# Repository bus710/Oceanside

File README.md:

# Oceanside

An integration project of RTOS, Golang application, and various clients.

## Maintainer
  
SJ Kim  
- Profile: [bus710.net](http://bus710.net)  
- Contact: <<bus710@gmail.com>>  

## Disclaimer

Using this project may cause various issue. Please consider your responsibility.

## Table of Contents
- Summary
- Hardware
- RTOS
- Golang Application 
- Clients
- Reference

## Summary

## Hardware

SBC, a bridge board, and a control board.

## RTOS

Chibios, threads, and the protocol.

## Golang Application

Termui, socket/websocket, and high performacne calcuration.

## Clients

Various clients such as ROS, LabVIEW, Unity3D, and so on.

## Reference

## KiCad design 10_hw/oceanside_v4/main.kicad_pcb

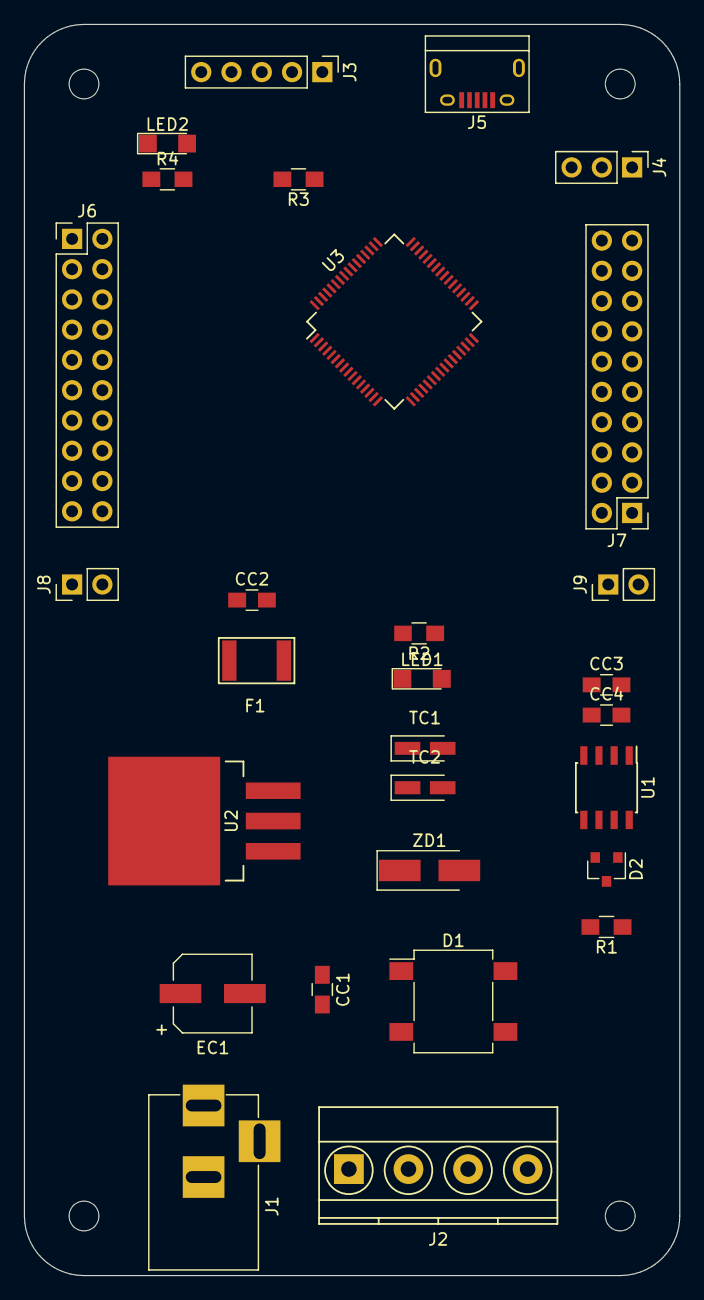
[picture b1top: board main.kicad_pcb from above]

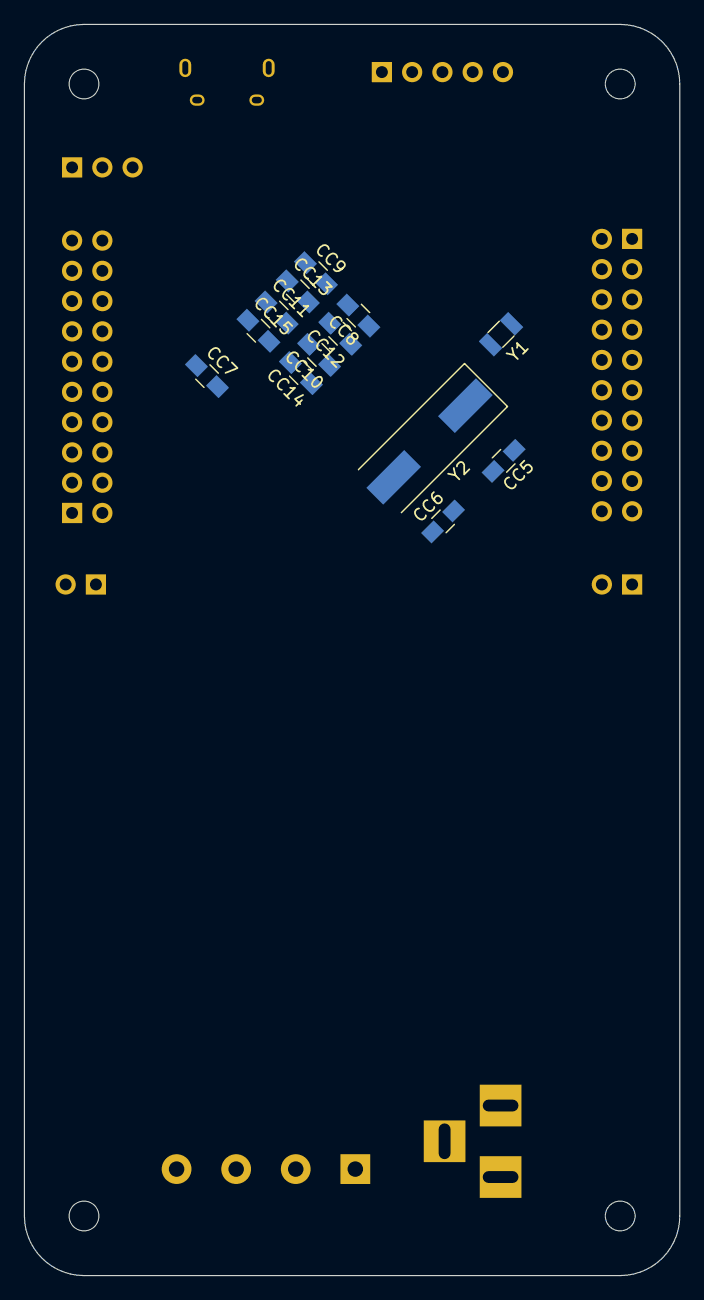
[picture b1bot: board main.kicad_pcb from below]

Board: 2 copper layers, 55.0 x 105.0 mm, 42 parts (13 on the bottom side), 60 nets, no tracks yet.

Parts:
CC1, CC2, CC3, CC8, CC9, CC10, CC11: 1uF; C_0805_HandSoldering
CC4, CC12, CC13, CC14, CC15: 4.7uF; C_0805_HandSoldering
CC5, CC6: 15pF; C_0805_HandSoldering
CC7: 2.2uF; C_0805_HandSoldering
D1: DF01S (OnSemi) +-AA; Diode_Bridge_DFS
D2: SM712; SOT-23
EC1: 47uF; CP_Elec_6.3x4.5
F1: FUSE(PTS18126V300); FusePTS1812
J1: BARREL_JACK
J2: VehicleCON; TerminalBlock_Pheonix_MKDS1.5-4pol
J3: SWDCON; Pin_Header_Straight_1x05_Pitch2.54mm
J4: SerialConsole; Pin_Header_Straight_1x03_Pitch2.54mm
J5: MiniUSB; USB_Micro-B
J6: GPIO_1; Pin_Header_Straight_2x10_Pitch2.54mm
J7: GPIO_2; Pin_Header_Straight_2x10_Pitch2.54mm
J8, J9: 3V3; Pin_Header_Straight_1x02_Pitch2.54mm
LED1, LED2: LED; LED_1206
R1: 120; R_0805_HandSoldering
R2, R4: 200; R_0805_HandSoldering
R3: 10k; R_0805_HandSoldering
TC1, TC2: 10uF; CP_Tantalum_Case-A_EIA-3216-18_Wave
U1: SN65HVD233-HT; SOIC-8_3.9x4.9mm_Pitch1.27mm
U2: LM1085-3.3/TO263; TO-263-3Lead_re
U3: STM32F446R; LQFP-64_10x10mm_Pitch0.5mm
Y1: 32k; Crystal_SMD_3215-2pin_3.2x1.5mm
Y2: 8M; Crystal_SMD_HC49-SD
ZD1: BZG05C12; D_SMA_Handsoldering

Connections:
+3V3: CC2.1, CC3.1, CC4.1, CC8.1, CC9.1, CC10.1, CC11.1, CC12.1, CC13.1, CC14.1, CC15.1, F1.1, J3.1, J8.1, J9.1, R2.2, R3.1, U1.3, U3.1, U3.13, U3.19, U3.32, U3.48, U3.64
/Battery+: D1.3, J1.1, J2.1
/SUB_F446/NRST: J3.5, R3.2, U3.7
/SUB_F446/OSC32_1: U3.3, Y1.2
/SUB_F446/OSC32_2: U3.4, Y1.1
/SUB_F446/OSC_1: CC5.1, U3.5, Y2.1
/SUB_F446/OSC_2: CC6.1, U3.6, Y2.2
/SUB_F446/P0: J6.1, U3.50
/SUB_F446/P1: J6.2, U3.51
/SUB_F446/P2: J6.3, U3.52
/SUB_F446/P3: J6.4, U3.53
/SUB_F446/P4: J6.5, U3.54
/SUB_F446/P5: J6.6, U3.55
/SUB_F446/P6: J6.7, U3.56
/SUB_F446/P7: J6.8, U3.57
/SUB_F446/P8: J6.9, U3.58
/SUB_F446/P9: J6.10, U3.59
/SUB_F446/P10: J6.11, U3.8
/SUB_F446/P11: J6.12, U3.9
/SUB_F446/P12: J6.13, U3.10
/SUB_F446/P13: J6.14, U3.11
/SUB_F446/P14: J6.15, U3.14
/SUB_F446/P15: J6.16, U3.15
/SUB_F446/P16: J6.17, U3.16
/SUB_F446/P17: J7.1, U3.17
/SUB_F446/P18: J7.2, U3.20
/SUB_F446/P19: J7.3, U3.21
/SUB_F446/P20: J7.4, U3.22
/SUB_F446/P21: J7.5, U3.23
/SUB_F446/P22: J7.6, U3.24
/SUB_F446/P23: J7.7, U3.25
/SUB_F446/P24: J7.8, U3.26
/SUB_F446/P25: J7.9, U3.27
/SUB_F446/P26: J7.10, U3.29
/SUB_F446/P27: J7.11, U3.33
/SUB_F446/P28: J7.12, U3.34
/SUB_F446/P29: J7.13, U3.35
/SUB_F446/P30: J7.14, U3.36
/SUB_F446/P31: J7.15, U3.37
/SUB_F446/P32: J7.16, U3.38
/SUB_F446/P33: J7.17, U3.39
/SUB_F446/P34: J7.18, U3.40
/SUB_F446/P35: J7.19, U3.41
/SUB_F446/STM_CAN1_RX: U1.4, U3.62
/SUB_F446/STM_CAN1_TX: U1.1, U3.61
/SUB_F446/SWCLK: J3.4, U3.49
/SUB_F446/SWDIO: J3.2, U3.46
/SUB_F446/SYS_LED: R4.1, U3.2
/SUB_F446/UART1_RX: J4.2, U3.43
/SUB_F446/UART1_TX: J4.1, U3.42
GND: CC1.2, CC2.2, CC3.2, CC4.2, CC5.2, CC6.2, CC7.2, CC8.2, CC9.2, CC10.2, CC11.2, CC12.2, CC13.2, CC14.2, CC15.2, D1.2, D1.4, D2.3, EC1.2, J1.2, J1.3, J2.2, J3.3, J4.3, J5.5, J5.6, J8.2, J9.2, LED1.1, LED2.1, TC1.2, TC2.2, U1.2, U1.8, U2.1, U3.12, U3.18, U3.28, U3.31, U3.47, U3.60, U3.63, ZD1.2
unnamed: CC1.1, D1.1, EC1.1, TC1.1, U2.3, ZD1.1
unnamed: CC7.1, U3.30
unnamed: D2.1, J2.3, R1.1, U1.7
unnamed: D2.2, J2.4, R1.2, U1.6
unnamed: F1.2, TC2.1, U2.2
unnamed: J5.2, U3.44
unnamed: J5.3, U3.45
unnamed: LED1.2, R2.1
unnamed: LED2.2, R4.2

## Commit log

2017-06-29 A minor update
2017-06-30 1st draft for readme.
2017-07-08 added the firmware.
2017-07-09 added uart feature but not tested yet.
2017-07-10 Rename 02_mbed.md to 02_chibios.md
2017-07-10 succeeded to activate CAN.
2017-07-10 added a comment about CAN1.
2017-07-10 added a new image.
2017-07-12 plotted the schematic pdf.
2017-07-12 schematic modified.
    CAN IC pin 8 should be connected to GND.
2017-07-12 the sample image is resized.
2017-07-12 code update to handle threads' code in each file.
2017-07-15 .
    added comments
    added to support stlink v2.
2017-07-19 testing uart and mailbox/messageQ
2017-07-20 worked on protocol.
2017-07-20 protocol document is started.
2017-07-21 receiving uart commands in both sides is tested.
2017-07-25 Defined the protocol between the board and SBC.
2017-08-11 added can rx code.
2017-08-15 can filter testing.
2017-08-24 oceanside_v4
